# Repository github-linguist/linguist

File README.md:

# Linguist

This library is used on GitHub.com to detect blob languages, ignore binary or vendored files, suppress generated files in diffs, and generate language breakdown graphs.

## Documentation

- [How Linguist works](/docs/how-linguist-works.md)
- [Change Linguist's behaviour with overrides](/docs/overrides.md)
- [Troubleshooting](/docs/troubleshooting.md)
- [Contributing guidelines](CONTRIBUTING.md)

## Installation

Install the gem:

```bash
gem install github-linguist
```

### Dependencies

Linguist is a Ruby library so you will need a recent version of Ruby installed.
There are known problems with the macOS/Xcode supplied version of Ruby that causes problems installing some of the dependencies.
Accordingly, we highly recommend you install a version of Ruby using Homebrew, `rbenv`, `rvm`, `ruby-build`, `asdf` or other packaging system, before attempting to install Linguist and the dependencies.

Linguist uses [`charlock_holmes`](https://github.com/brianmario/charlock_holmes) for character encoding and [`rugged`](https://github.com/libgit2/rugged) for libgit2 bindings for Ruby.
These components have their own dependencies.

1. charlock_holmes
    * cmake
    * pkg-config
    * [ICU](http://site.icu-project.org/)
    * [zlib](https://zlib.net/)
2. rugged
    * [libcurl](https://curl.haxx.se/libcurl/)
    * [OpenSSL](https://www.openssl.org)

You may need to install missing dependencies before you can install Linguist.
For example, on macOS with [Homebrew](http://brew.sh/):

```bash
brew install cmake pkg-config icu4c
```

On Ubuntu:

```bash
sudo apt-get install build-essential cmake pkg-config libicu-dev zlib1g-dev libcurl4-openssl-dev libssl-dev ruby-dev
```

## Usage

### Application usage

Linguist can be used in your application as follows:

```ruby
require 'rugged'
require 'linguist'

repo = Rugged::Repository.new('.')
project = Linguist::Repository.new(repo, repo.head.target_id)
project.language       #=> "Ruby"
project.languages      #=> { "Ruby" => 119387 }
```

### Command line usage

The `github-linguist` executable operates in two distinct modes:

1. **[Git Repository mode](#git-repository)** - Analyzes an entire Git repository (when given a directory path or no path)
2. **[Single file mode](#single-file)** - Analyzes a specific file (when given a file path)

#### Git Repository

A repository's languages stats can be assessed from the command line using the `github-linguist` executable.
Without any options, `github-linguist` will output the language breakdown by percentage and file size.

```bash
cd /path-to-repository
github-linguist
```

You can try running `github-linguist` on the root directory in this repository itself:

```console
$ github-linguist
66.84%  264519     Ruby
24.68%  97685      C
6.57%   25999      Go
1.29%   5098       Lex
0.32%   1257       Shell
0.31%   1212       Dockerfile
```

#### Additional options

##### `--rev REV`

The `--rev REV` flag will change the git revision being analyzed to any [gitrevisions(1)](https://git-scm.com/docs/gitrevisions#_specifying_revisions) compatible revision you specify.

This is useful to analyze the makeup of a repo as of a certain tag, or in a certain branch.

For example, here is the popular [Jekyll open source project](https://github.com/jekyll/jekyll).

```console
$ github-linguist jekyll

70.64%  709959     Ruby
23.04%  231555     Gherkin
3.80%   38178      JavaScript
1.19%   11943      HTML
0.79%   7900       Shell
0.23%   2279       Dockerfile
0.13%   1344       Earthly
0.10%   1019       CSS
0.06%   606        SCSS
0.02%   234        CoffeeScript
0.01%   90         Hack
```

And here is Jekyll's published website, from the gh-pages branch inside their repository.

```console
$ github-linguist jekyll --rev origin/gh-pages
100.00% 2568354    HTML
```

##### `--breakdown`

The `--breakdown` or `-b` flag will additionally show the breakdown of files by language.

You can try running `github-linguist` on the root directory in this repository itself:

```console
$ github-linguist --breakdown
66.84%  264519     Ruby
24.68%  97685      C
6.57%   25999      Go
1.29%   5098       Lex
0.32%   1257       Shell
0.31%   1212       Dockerfile

Ruby:
Gemfile
Rakefile
bin/git-linguist
bin/github-linguist
ext/linguist/extconf.rb
github-linguist.gemspec
lib/linguist.rb
…
```

##### `--strategies`

The `--strategies` or `-s` flag will show the language detection strategy used for each file. This is useful for understanding how Linguist determined the language of specific files. Note that unless the `--json` flag is specified, this flag will set the `--breakdown` flag implicitly.

You can try running `github-linguist` on the root directory in this repository itself with the strategies flag:

```console
$ github-linguist --breakdown --strategies
66.84%  264519     Ruby
24.68%  97685      C
6.57%   25999      Go
1.29%   5098       Lex
0.32%   1257       Shell
0.31%   1212       Dockerfile

Ruby:
  Gemfile [Filename]
  Rakefile [Filename]
  bin/git-linguist [Extension]
  bin/github-linguist [Extension]
  lib/linguist.rb [Extension]
  …
```

If a file's language is affected by `.gitattributes`, the strategy will show the original detection method along with a note indicating whether the gitattributes setting changed the result or confirmed it.

For instance, if you had the following .gitattributes overrides in your repo:

```gitattributes

*.ts linguist-language=JavaScript
*.js linguist-language=JavaScript

```

the output of Linguist would be something like this:

```console
100.00% 217        JavaScript

JavaScript:
  demo.ts [Heuristics (overridden by .gitattributes)]
  demo.js [Extension (confirmed by .gitattributes)]
```

##### `--json`

The `--json` or `-j` flag output the data into JSON format.

```console
$ github-linguist --json
{"Dockerfile":{"size":1212,"percentage":"0.31"},"Ruby":{"size":264519,"percentage":"66.84"},"C":{"size":97685,"percentage":"24.68"},"Lex":{"size":5098,"percentage":"1.29"},"Shell":{"size":1257,"percentage":"0.32"},"Go":{"size":25999,"percentage":"6.57"}}
```

This option can be used in conjunction with `--breakdown` to get a full list of files along with the size and percentage data.

```console
$ github-linguist --breakdown --json
{"Dockerfile":{"size":1212,"percentage":"0.31","files":["Dockerfile","tools/grammars/Dockerfile"]},"Ruby":{"size":264519,"percentage":"66.84","files":["Gemfile","Rakefile","bin/git-linguist","bin/github-linguist","ext/linguist/extconf.rb","github-linguist.gemspec","lib/linguist.rb",...]}}

```

NB. The `--strategies` flag has no effect, when the `--json` flag is present.

#### Single file

Alternatively you can find stats for a single file using the `github-linguist` executable.

You can try running `github-linguist` on files in this repository itself:

```console
$ github-linguist grammars.yml
grammars.yml: 884 lines (884 sloc)
  type:      Text
  mime type: text/x-yaml
  language:  YAML
```

#### Additional options

##### `--breakdown`

This flag has no effect in *Single file* mode.

##### `--strategies`

When using the `--strategies` or `-s` flag with a single file, you can see which detection method was used:

```console
$ github-linguist --strategies lib/linguist.rb 
lib/linguist.rb: 105 lines (96 sloc)
  type:      Text
  mime type: application/x-ruby
  language:  Ruby
  strategy:  Extension
```

If a file's language is affected by `.gitattributes`, the strategy will show whether the gitattributes setting changed the result or confirmed it:

In this fictitious example, it says "confirmed by .gitattributes" since the detection process (using the Filename strategy) would have given the same output as the override:
```console
.devcontainer/devcontainer.json: 27 lines (27 sloc)
  type:      Text
  mime type: application/json
  language:  JSON with Comments
  strategy:  Filename (confirmed by .gitattributes)
```

In this other fictitious example, it says "overridden by .gitattributes" since the gitattributes setting changes the detected language to something different:

```console
test.rb: 13 lines (11 sloc)
  type:      Text
  mime type: application/x-ruby
  language:  Java
  strategy:  Extension (overridden by .gitattributes)
```

Here, the `.rb` file would normally be detected as Ruby by the Extension strategy, but `.gitattributes` overrides it to be detected as Java instead.

##### `--json`

Using the `--json` flag will give you the output for a single file in JSON format:

```console
$ github-linguist --strategies --json  lib/linguist.rb
{"lib/linguist.rb":{"lines":105,"sloc":96,"type":"Text","mime_type":"application/x-ruby","language":"Ruby","large":false,"generated":false,"vendored":false}}
```

NB. The `--strategies` has no effect, when the `--json` flag is present.

#### Docker

If you have Docker installed you can either build or use
our pre-built images and run Linguist within a container:

```console
$ docker run --rm -v $(pwd):$(pwd):Z -w $(pwd) -t ghcr.io/github-linguist/linguist:latest
66.84%  264519     Ruby
24.68%  97685      C
6.57%   25999      Go
1.29%   5098       Lex
0.32%   1257       Shell
0.31%   1212       Dockerfile
```

##### Building the image

```console
$ docker build -t linguist .
$ docker run --rm -v $(pwd):$(pwd):Z -w $(pwd) -t linguist
66.84%  264519     Ruby
24.68%  97685      C
6.57%   25999      Go
1.29%   5098       Lex
0.32%   1257       Shell
0.31%   1212       Dockerfile
$ docker run --rm -v $(pwd):$(pwd) -w $(pwd) -t linguist github-linguist --breakdown
66.84%  264519     Ruby
24.68%  97685      C
6.57%   25999      Go
1.29%   5098       Lex
0.32%   1257       Shell
0.31%   1212       Dockerfile

Ruby:
Gemfile
Rakefile
bin/git-linguist
bin/github-linguist
ext/linguist/extconf.rb
github-linguist.gemspec
lib/linguist.rb
…
```

## Contributing

Please check out our [contributing guidelines](CONTRIBUTING.md).

## License

The language grammars included in this gem are covered by their repositories' respective licenses.
[`vendor/README.md`](/vendor/README.md) lists the repository for each grammar.

All other files are covered by the MIT license, see [`LICENSE`](./LICENSE).

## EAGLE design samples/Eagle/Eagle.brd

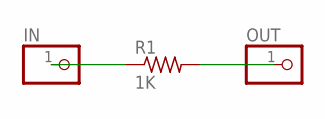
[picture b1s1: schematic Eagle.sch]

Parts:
IN: PINHD-1X1; 1X01
OUT: PINHD-1X1; 1X01
R1: 1K; R0805

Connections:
unnamed: IN.1, R1.1
unnamed: OUT.1, R1.2

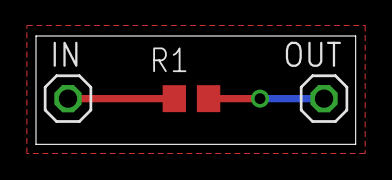
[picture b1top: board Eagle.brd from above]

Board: 2 copper layers, 17.8 x 6.0 mm, 3 parts (0 on the bottom side), 2 nets.
